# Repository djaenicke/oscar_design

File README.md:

# robo_car
Robot car platform used for developing autonomous vehicle concepts

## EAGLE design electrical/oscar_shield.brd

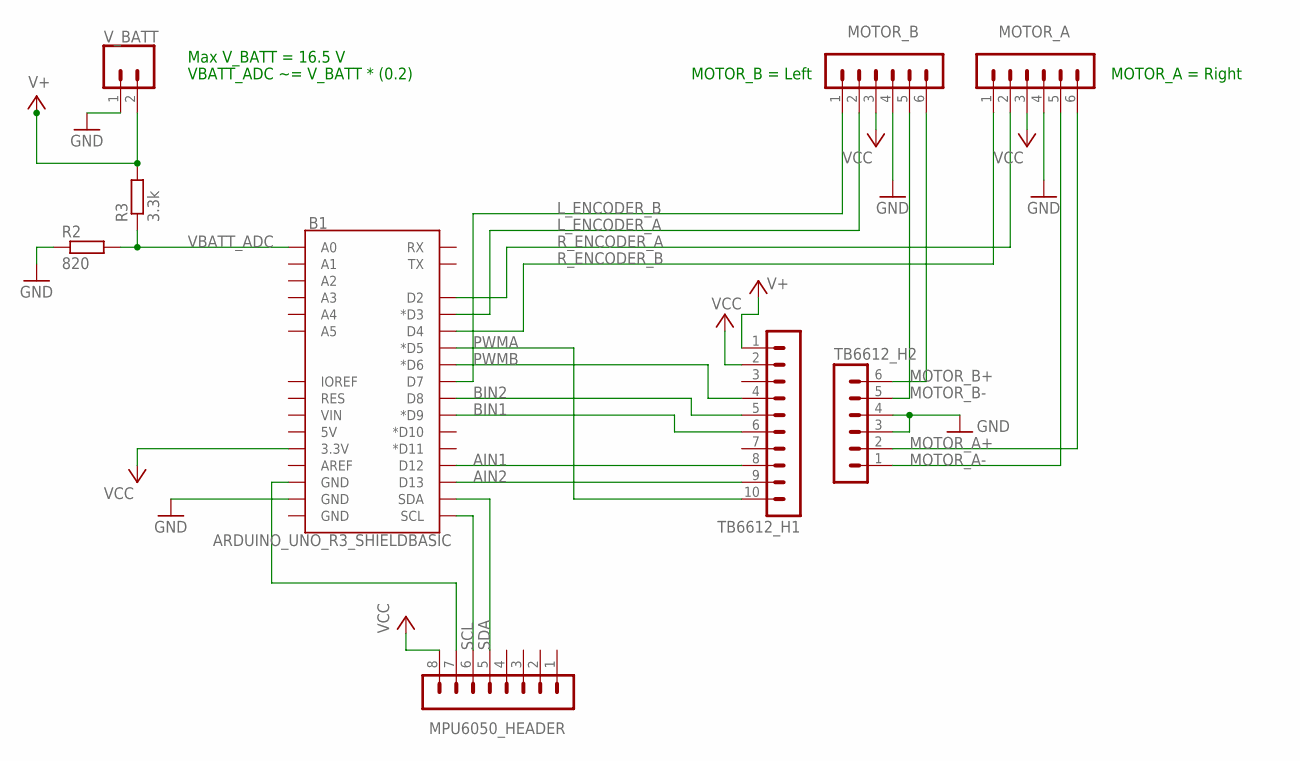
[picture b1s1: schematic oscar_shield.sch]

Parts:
B1: ARDUINO_UNO_R3_SHIELDBASIC; UNO_R3_SHIELD
MOTOR_A: MA06-1
MOTOR_B: MA06-1
MPU6050_HEADER: MA08-1
R2: 820; 0207/10
R3: 3.3k; 0207/10
TB6612_H1: MA10-1
TB6612_H2: MA06-1
V_BATT: CONN_025MM; SCREWTERMINAL-5MM-2

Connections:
AIN1: B1.D12, TB6612_H1.8
AIN2: B1.D13, TB6612_H1.9
BIN1: B1.D9 (*D9), TB6612_H1.6
BIN2: B1.D8, TB6612_H1.5
GND: B1.GND@1 (GND), MOTOR_A.4, MOTOR_B.4, R2.1, TB6612_H2.3, TB6612_H2.4, V_BATT.1
L_ENCODER_A: B1.D3 (*D3), MOTOR_B.2
L_ENCODER_B: B1.D7, MOTOR_B.1
MOTOR_A+: MOTOR_A.6, TB6612_H2.2
MOTOR_A-: MOTOR_A.5, TB6612_H2.1
MOTOR_B+: MOTOR_B.6, TB6612_H2.6
MOTOR_B-: MOTOR_B.5, TB6612_H2.5
unnamed: B1.GND@2 (GND), MPU6050_HEADER.7
PWMA: B1.D5 (*D5), TB6612_H1.10
PWMB: B1.D6 (*D6), TB6612_H1.4
R_ENCODER_A: B1.D2, MOTOR_A.2
R_ENCODER_B: B1.D4, MOTOR_A.1
SCL: B1.SCL, MPU6050_HEADER.6
SDA: B1.SDA, MPU6050_HEADER.5
V+: R3.2, TB6612_H1.1, V_BATT.2
VBATT_ADC: B1.A0, R2.2, R3.1
VCC: B1.3.3V, MOTOR_A.3, MOTOR_B.3, MPU6050_HEADER.8, TB6612_H1.2

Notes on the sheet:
Max V_BATT = 16.5 V
VBATT_ADC ~= V_BATT * (0.2)
MOTOR_A = Right
MOTOR_B = Left

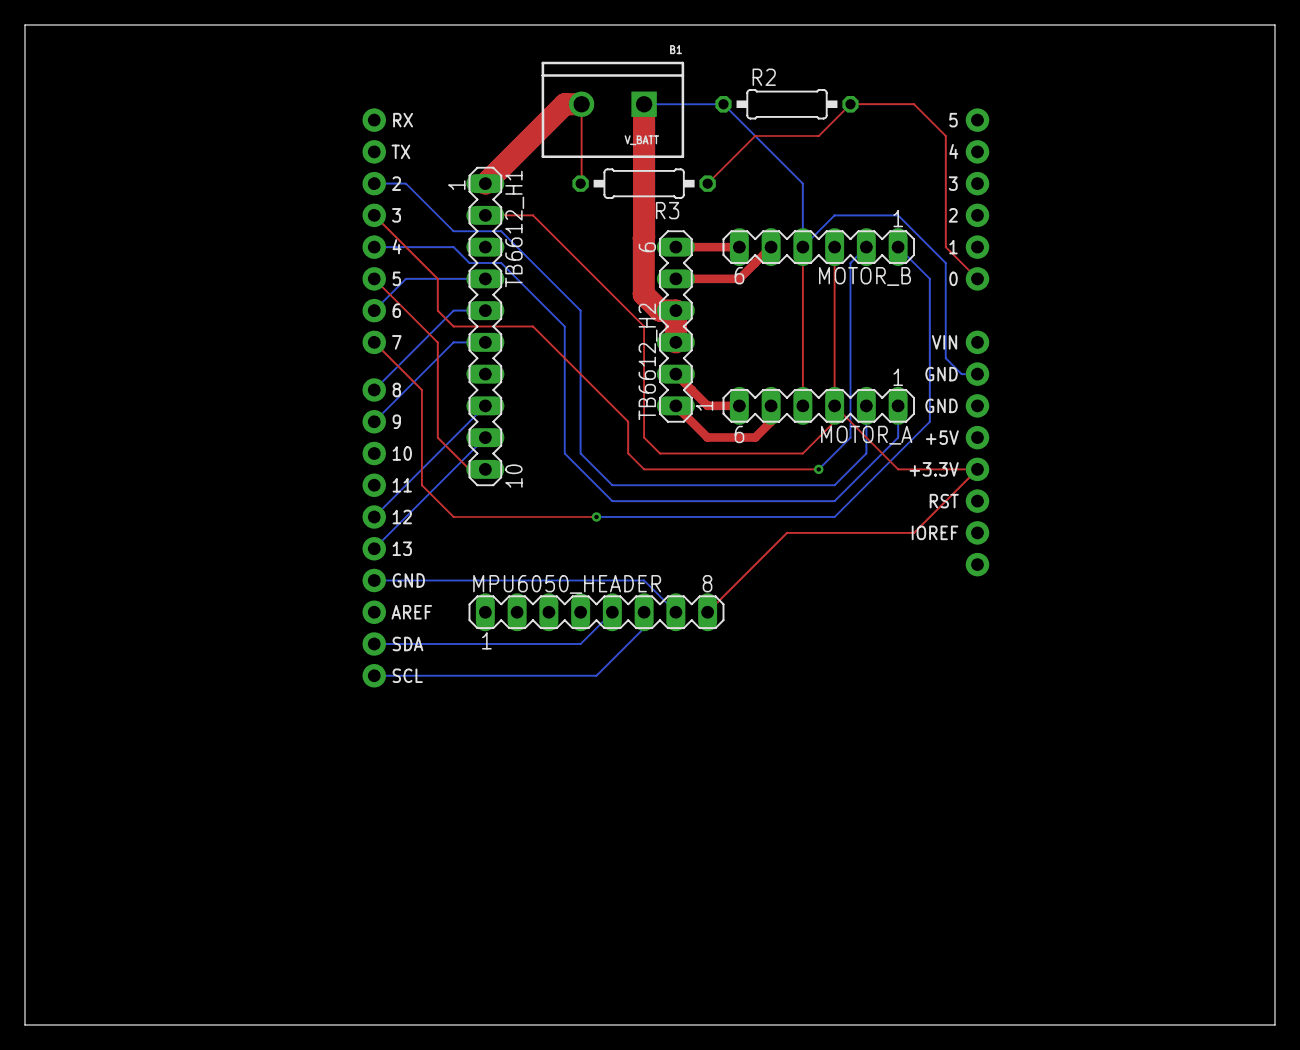
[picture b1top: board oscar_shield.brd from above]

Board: 2 copper layers, 100.0 x 80.0 mm, 9 parts (0 on the bottom side), 21 nets.

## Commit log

2019-06-07 Added the MCUexpresso project
2019-06-07 Updated core clock to 120 MHz
    Also, the default board files were replaced with empty files.
2019-06-08 Updates to get the motors working (no speed control yet)
2019-06-08 Added the ability to control the motor speed via PWM
2019-06-09 Added a class for controlling the object sensor servo
2019-06-09 Added bluetooth control
2019-06-11 Added a battery monitor to measure the battery voltage
2019-06-14 Added wheel speed sensors
2019-06-16 Updated SDK to add SD card
2019-06-16 Added tasks
2019-06-16 Updated further to include SD card support
2019-06-16 SD card is being recognized
2019-06-17 Minor changes
2019-06-19 Added data logging
2019-06-19 Fixed bug with rr wheel speed getting corrupted
2019-06-20 Moved to period based encoder measurement
    There are no issues with 0 rad/s readings when the data logging is disabled. When it's enabled, there are issues with the readings.
2019-06-20 Added a simple filter to the wheel speed calculation
2019-06-21 Wheel speeds are decent at 25ms sample rate...
2019-06-21 Tried to account for missing a measurement...
    Still not great performance
2019-06-23 Simplified the wheel speed measurements
2019-06-23 Added a simple low pass filter
2019-06-25 Added a PID class
2019-06-28 Moved the wheel speed filtering out of the interrupt
2019-06-30 Wheel speeds measurements are good
2019-06-30 Minor update to remove magic number
2019-06-30 Reworked the data logging
2019-06-30 Implemented the PID controllers
    PID controller is working well under no-load conditions
2019-06-30 More PID controller changes...
    PID is still not working very well
2019-07-02 Removed the two front wheel speed sensors
    The two right and two left motors cannot be controlled independently
2019-07-02 Minor updates
2019-07-03 PID is working!
2019-07-03 Updated to fix open loop mode
2019-07-03 Adding matlab scripts used for offline analysis
2019-07-04 Added init routine for object detection
2019-07-04 Added the object detection task
2019-07-04 Updated Servo class to use more encapsulation
2019-07-04 Added initial ultrasonic sensor code
2019-07-04 Updated servo class to work with any FTM
    This isn't quite done yet. Need a way to redirect the ISRs
2019-07-04 Servo class can now be instaniated multiple times
2019-07-04 UltrasonicSensor now supports multiple instantiation
2019-07-04 Added more USS code
    USS doesn't seem to provide accurate distances to objects.
2019-07-05 Added a port ISR router module
2019-07-05 Added comments in Servo and UltrasonicSensor classes
2019-07-06 Ultrasonic sensor is working
2019-07-06 Added simple detection array
2019-07-06 Reduced turning speeds for controllability
2019-07-07 Added object detection override
2019-07-07 Added IMU initialization code
2019-07-10 Added code to read the acceleration
2019-07-13 Added MPU6050 class
    - Need to add a delay based on the FTM
    - Need to allow the I2C channel to be configurable
2019-07-13 Added MPU6050 object for more inertial measurements to IMU.cpp
2019-07-14 Acceleration readings are good from MPU6050
2019-07-14 Added gyro readings from MPU6050
2019-07-20 Added filtering to battery measurement
2019-07-20 Created a separate class for the onboard 6-axis sensor
2019-07-27 Flipped the direction for the new motors
2019-07-27 Updated io abstraction
2019-07-27 Bug fixes...
2019-07-27 Switched the speed controller to use the hall effect speed sensors
2019-07-28 Switched hall effect sensors to use period measurement
2019-07-28 Missed from previous commit
2019-07-28 Switched the debug console from semihosting to UART
2019-07-28 Retuned based on system identification
2019-07-28 Bug fix for reverse
2019-07-28 Minor change
2019-07-28 Created behaviors.cpp
2019-07-28 Moved wheel speed measurements to inertial_states.cpp
2019-07-28 Implemented go-to-point behavior
2019-07-30 Added the ability to enable/disable autonomous mode
2019-11-10 Fixed open loop mode and made it easier to log results
2019-11-10 Added data
2019-11-10 Removed optical encoder measurements
    Closed loop is still functional
2019-11-10 Removed min period check
2019-11-10 Updated data
2019-11-29 Added a new simulation with both motors
2019-11-29 Deleted old simulations
2019-11-29 Updated tuning parameters and improved stoping distance
2019-11-29 Collected more data
2019-11-29 Added the wheel speed filters into the simulation
2019-11-30 Added MATLAB scripts for FFT based method for measuring wheel speeds
2019-11-30 Added CMSIS DSP library
2019-11-30 Added an FFT test using hardcoded data
2019-12-01 N=1024 seems to be the sweet spot
    N=1024 provides a good tradeoff between execution time and wheel speed measurement accuracy.
2019-12-01 Created new module to run the wheel speed FFTs
2019-12-01 Wheel speed measureme nt via FFT method is working.
2019-12-04 Updated matlab scripts for data analysis
2019-12-07 Updated GoToPointController
2019-12-07 GTP controller is working
    GTP controller is working as well as it's going to until an EKF is added to improve position and heading feedback.
2019-12-15 Initial steps for developing Kalman filters
2019-12-15 Fixed the fft_test
2019-12-23 removed fft wheel speed measurements
2019-12-24 Project updates for MCUexpresso v11.1.0
2019-12-24 Updated to SDK v2.7
2019-12-24 Ethernet is working
2019-12-26 Added Network_Status check
2019-12-26 Updated folder structure
2019-12-26 Initial implementation of a simple UDP client class
2019-12-26 Refactoring
2019-12-26 UDP receive is working
2019-12-26 Updated to support rx datagrams larger than 1500 bytes
2019-12-27 Car is functional with Ethernet disabled
2019-12-28 Added ROS client lib
2019-12-28 ROS client is now working!
2019-12-29 refactoring to make it easier to interface with ROS
2019-12-29 Added imu and odometry messages
2019-12-31 Fixed asserts in debug mode...
2019-12-31 removed extra files
2019-12-31 abstracted HW interface from mpu6050 class
2019-12-31 added FXOS accel measurement
2020-01-01 Added accel bias compensation to FX0S sensor
2020-01-04 Added software based acceleration bias compensation for the FXOS sensor
2020-01-05 Clean up
2020-03-06 `vallen` is verified to be less than `len`, therefore, it can never be the case that `vallen >= len + sizeof(rhostname)`.
    This PR fixes the check so the `rhostname` array does not overflow.
    Reported-by: Github Security Lab <securitylab@github.com>
2020-03-31 modeling updates
2020-04-04 Updated for new controller tuning
2020-05-10 Deleting original K64F software
    K64F software is fully ported to mbed OS for sharability
2020-05-10 Deleting unused scripts
2020-05-10 Added shield schematic/pcb and mechanical part drawings
2020-05-19 Added sensor characterization data
2020-06-21 Adding new parts for v2 of the platform
2020-11-29 Added v3 mechanical design
2020-11-29 Updated schematic and board layout

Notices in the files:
parts and their libraries:
SparkFun-Boards: Licensing: Creative Commons ShareAlike 4.0 International - https://creativecommons.org/licenses/by-sa/4.0
